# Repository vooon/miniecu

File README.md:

miniECU
=======

miniECU - monitoring unit for model gasoline engines with kill switch.

TBD

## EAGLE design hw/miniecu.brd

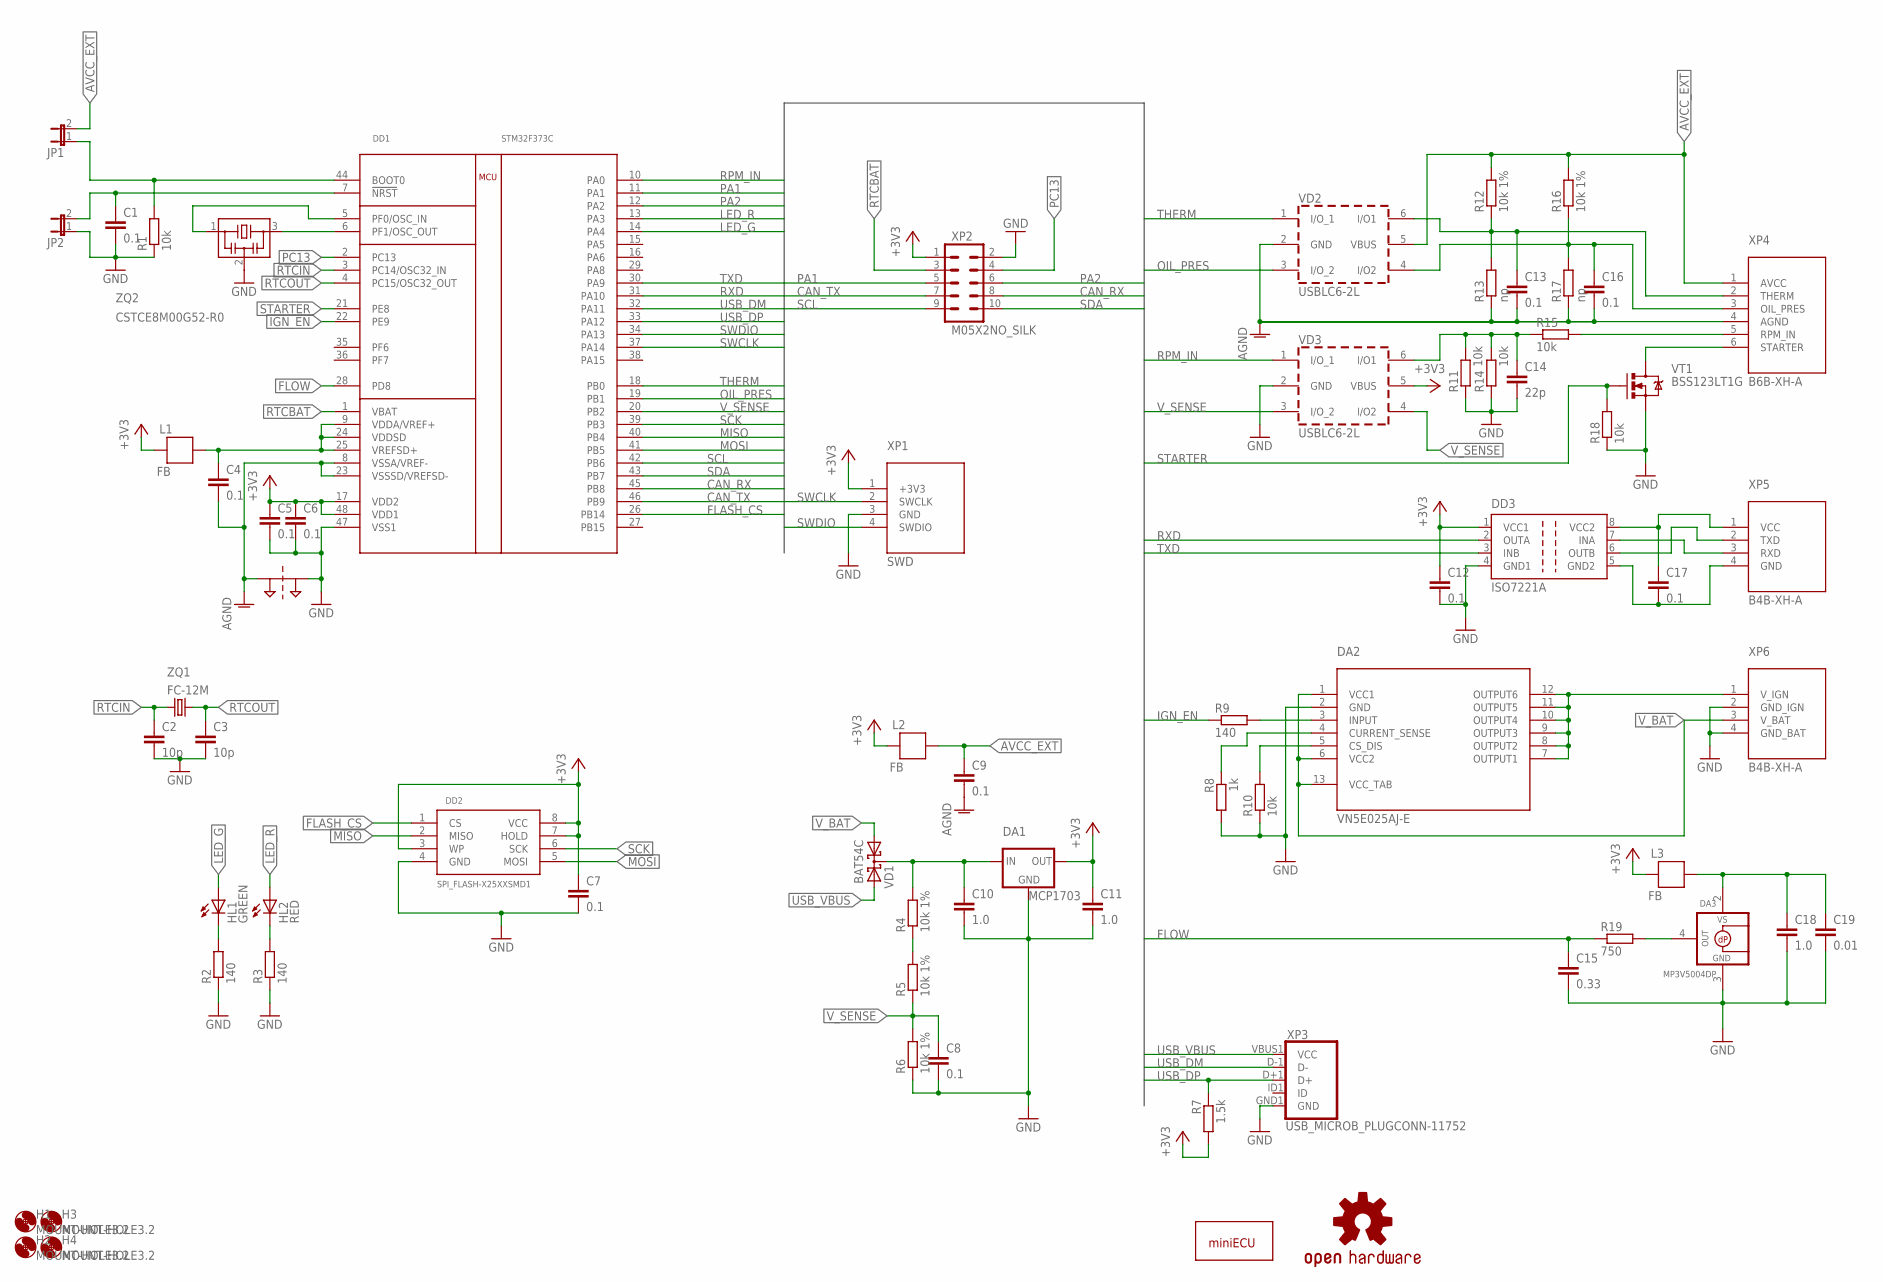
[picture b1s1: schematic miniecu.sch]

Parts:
C1, C4, C5, C6, C7, C8, C9, C12, C13, C16, C17: 0.1; C0603
C2, C3: 10p; C0603
C10, C11, C18: 1.0; C0805
C14: 22p; C0603
C15: 0.33; C0603
C19: 0.01; C0603
DA1: MCP1703; SOT23
DA2: VN5E025AJ-E; POWERSSO-12
DA3: MP3V5004DP; SOP8-1351
DD1: STM32F373C; LQFP48
DD2: SPI_FLASH-X25XXSMD1; SO08-EIAJ
DD3: ISO7221A; SO-08
H1, H2, H3, H4: MOUNT-HOLE3.2; 3,2
HL1: GREEN; LED-0603
HL2: RED; LED-0603
JP1, JP2: JUMPER-2SMD-NO; SJ_2S-NO
L1, L2, L3: FB; 0603
LOGO1: MINIECU_LOGO
LOGO2: OSHW-LOGOL; OSHW-LOGO-L
PT1: 2PT_GND_TIE
R1, R10, R11, R14, R15, R18: 10k; R0603
R2, R3, R9: 140; R0603
R4, R5, R6, R12, R16: 10k 1%; R0805
R7: 1.5k; R0603
R8: 1k; R0603
R13, R17: np; R0805
R19: 750; R0603
VD1: BAT54C; SOT23
VD2, VD3: USBLC6-2L; SOT-23-6L
VT1: BSS123LT1G; SOT23
XP1: SWD; 1X04-1.27MM
XP2: M05X2NO_SILK; 2X5_NOSILK
XP3: USB_MICROB_PLUGCONN-11752; USB-B-MICRO-SMD_V03
XP4: B6B-XH-A; B6B-XH
XP5, XP6: B4B-XH-A; B4B-XH
ZQ1: FC-12M
ZQ2: CSTCE8M00G52-R0; CSTCE

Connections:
!NRST: C1.1, DD1.7 (!NRST), JP2.2
+3V3: C5.1, C6.1, C7.1, C11.1, C12.1, DA1.2 (OUT), DD1.17 (VDD2), DD1.48 (VDD1), DD2.3 (WP), DD2.7 (HOLD), DD2.8 (VCC), DD3.1 (VCC1), L1.2, L2.2, L3.2, R7.2, VD3.5 (VBUS), XP1.1 (+3V3), XP2.1
AGND: C4.2, C9.2, C13.2, C16.2, DD1.8 (VSSA/VREF-), DD1.23 (VSSSD/VREFSD-), PT1.P$1, R13.1, R17.1, VD2.2 (GND), XP4.4 (AGND)
AVCC: C4.1, DD1.9 (VDDA/VREF+), DD1.24 (VDDSD), DD1.25 (VREFSD+), L1.1
AVCC_EXT: C9.1, JP1.2, L2.1, R12.2, R16.2, VD2.5 (VBUS), XP4.1 (AVCC)
AVCC_FLOW: C18.1, C19.1, DA3.2 (VS), L3.1
BOOT0: DD1.44 (BOOT0), JP1.1, R1.2
CAN_RX: DD1.45 (PB8), XP2.8
CAN_TX: DD1.46 (PB9), XP2.7
FLASH_CS: DD1.26 (PB14), DD2.1 (CS)
FLOW: C15.1, DD1.28 (PD8), R19.1
GND: C1.2, C2.2, C3.2, C5.2, C6.2, C7.2, C8.2, C10.2, C11.2, C12.2, C14.2, C15.2, C18.2, C19.2, DA1.1 (GND), DA2.2 (GND), DA3.3 (GND), DD1.47 (VSS1), DD2.4 (GND), DD3.4 (GND1), JP2.1, PT1.P$2, R1.1, R2.1, R3.1, R6.1, R8.2, R10.1, R11.1, R14.1, R18.1, VD3.2 (GND), VT1.2 (S), XP1.3 (GND), XP2.2, XP3.GND1 (GND), XP6.2 (GND_IGN), XP6.4 (GND_BAT), ZQ2.2
GND2: C17.2, DD3.5 (GND2), XP5.4 (GND)
IGN_EN: DD1.22 (PE9), R9.1
IORXD: DD3.7 (INA), XP5.3 (RXD)
IOTXD: DD3.6 (OUTB), XP5.2 (TXD)
LED_G: DD1.14 (PA4), HL1.A
LED_R: DD1.13 (PA3), HL2.A
MISO: DD1.40 (PB4), DD2.2 (MISO)
MOSI: DD1.41 (PB5), DD2.5 (MOSI)
unnamed: R4.1, R5.2
unnamed: DA2.4 (CURRENT_SENSE), R8.1
unnamed: HL2.C, R3.2
unnamed: DA3.4 (+VOUT), R19.2
unnamed: HL1.C, R2.2
unnamed: C10.1, DA1.3 (IN), R4.2, VD1.3 (CC)
unnamed: DA2.3 (INPUT), R9.2
unnamed: DA2.5 (CS_DIS), R10.2
OIL_PRES: C16.1, DD1.19 (PB1), R16.1, R17.2, VD2.3 (I/O_2), VD2.4 (I/O2), XP4.3 (OIL_PRES)
OSC_IN: DD1.5 (PF0/OSC_IN), ZQ2.1
OSC_OUT: DD1.6 (PF1/OSC_OUT), ZQ2.3
PA1: DD1.11 (PA1), XP2.5
PA2: DD1.12 (PA2), XP2.6
PC13: DD1.2 (PC13), XP2.4
RPM_IN: C14.1, DD1.10 (PA0), R11.2, R14.2, R15.1, VD3.1 (I/O_1), VD3.6 (I/O1)
RPM_IN_CON: R15.2, XP4.5 (RPM_IN)
RTCBAT: DD1.1 (VBAT), XP2.3
RTCIN: C2.1, DD1.3 (PC14/OSC32_IN), ZQ1.1
RTCOUT: C3.1, DD1.4 (PC15/OSC32_OUT), ZQ1.2
RXD: DD1.31 (PA10), DD3.2 (OUTA)
SCK: DD1.39 (PB3), DD2.6 (SCK)
SCL: DD1.42 (PB6), XP2.9
SDA: DD1.43 (PB7), XP2.10
STARTER: DD1.21 (PE8), R18.2, VT1.1 (G)
STARTER_OUT: VT1.3 (D), XP4.6 (STARTER)
SWCLK: DD1.37 (PA14), XP1.2 (SWCLK)
SWDIO: DD1.34 (PA13), XP1.4 (SWDIO)
THERM: C13.1, DD1.18 (PB0), R12.1, R13.2, VD2.1 (I/O_1), VD2.6 (I/O1), XP4.2 (THERM)
TXD: DD1.30 (PA9), DD3.3 (INB)
USB_DM: DD1.32 (PA11), XP3.D-1 (D-)
USB_DP: DD1.33 (PA12), R7.1, XP3.D+1 (D+)
USB_VBUS: VD1.2 (A2), XP3.VBUS1 (VCC)
VCC2: C17.1, DD3.8 (VCC2), XP5.1 (VCC)
V_BAT: DA2.1 (VCC1), DA2.6 (VCC2), DA2.13 (VCC_TAB), VD1.1 (A1), XP6.3 (V_BAT)
V_IGN: DA2.7 (OUTPUT1), DA2.8 (OUTPUT2), DA2.9 (OUTPUT3), DA2.10 (OUTPUT4), DA2.11 (OUTPUT5), DA2.12 (OUTPUT6), XP6.1 (V_IGN)
V_SENSE: C8.1, DD1.20 (PB2), R5.1, R6.2, VD3.3 (I/O_2), VD3.4 (I/O2)

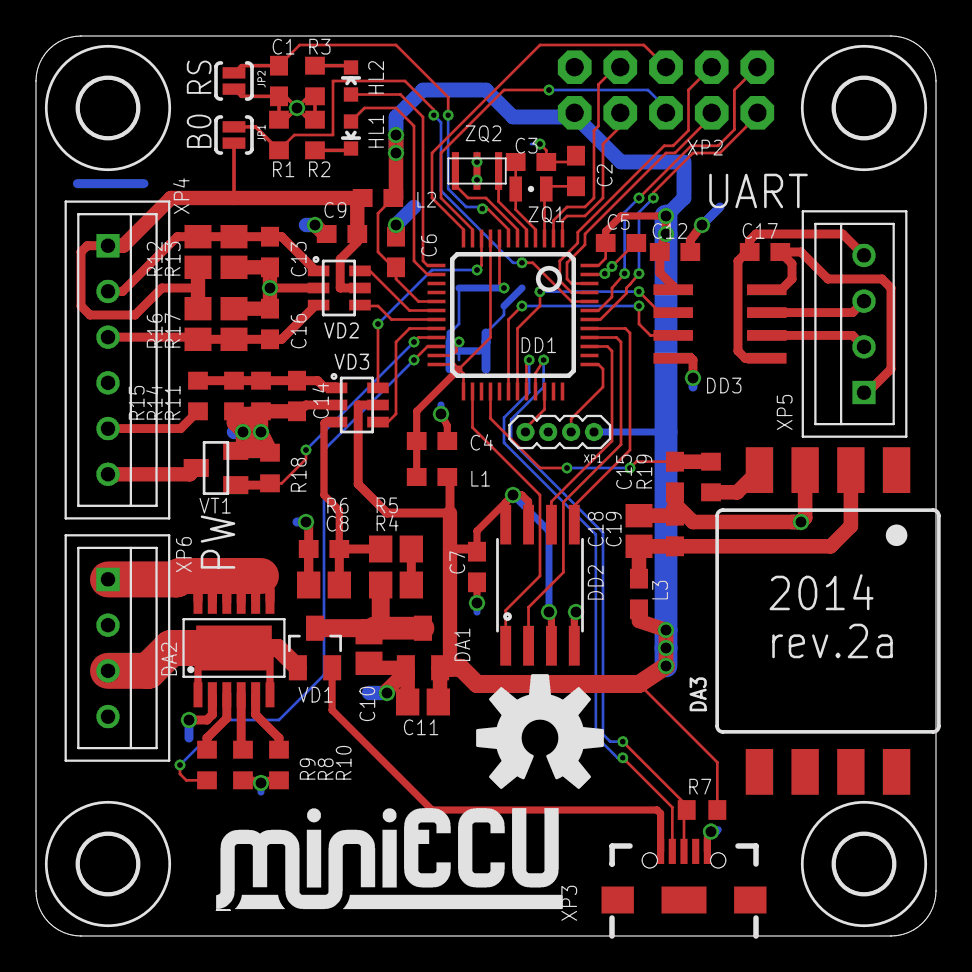
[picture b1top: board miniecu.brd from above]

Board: 2 copper layers, 50.0 x 50.0 mm, 70 parts (1 on the bottom side), 56 nets.

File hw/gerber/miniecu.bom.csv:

"Qty";"Value";"Device";"Package";"Parts";"Description";"FREQUENCY";"MF";"MPN";"OC_FARNELL";"OC_MOUSER";"OC_NEWARK";"PROD_ID";"VALUE";
"2";"";"JUMPER-2SMD-NO";"SJ_2S-NO";"JP1, JP2";"Jumper";"";"";"";"";"";"";"";"";
"1";"0.01";"C-EUC0603";"C0603";"C19";"CAPACITOR, European symbol";"";"";"";"";"";"";"";"";
"11";"0.1";"C-EUC0603";"C0603";"C1, C4, C5, C6, C7, C8, C9, C12, C13, C16, C17";"CAPACITOR, European symbol";"";"";"";"";"";"";"";"";
"1";"0.33";"C-EUC0603";"C0603";"C15";"CAPACITOR, European symbol";"";"";"";"";"";"";"";"";
"3";"1.0";"C-EUC0805";"C0805";"C10, C11, C18";"CAPACITOR, European symbol";"";"";"";"";"";"";"";"";
"1";"1.5k";"R-EU_R0603";"R0603";"R7";"RESISTOR, European symbol";"";"";"";"";"";"";"";"";
"6";"10k";"R-EU_R0603";"R0603";"R1, R10, R11, R14, R15, R18";"RESISTOR, European symbol";"";"";"";"";"";"";"";"";
"5";"10k 1%";"R-EU_R0805";"R0805";"R4, R5, R6, R12, R16";"RESISTOR, European symbol";"";"";"";"";"";"";"";"";
"3";"140";"R-EU_R0603";"R0603";"R2, R3, R9";"RESISTOR, European symbol";"";"";"";"";"";"";"";"";
"1";"1k";"R-EU_R0603";"R0603";"R8";"RESISTOR, European symbol";"";"";"";"";"";"";"";"";
"1";"22p";"C-EUC0603";"C0603";"C14";"CAPACITOR, European symbol";"";"";"";"";"";"";"";"";
"1";"2PT_GND_TIE";"2PT_GND_TIE";"2PT_GND_TIE";"PT1";"Package for connecting two ground nets in one place.";"";"";"";"";"";"";"";"";
"2";"6p";"C-EUC0603";"C0603";"C2, C3";"CAPACITOR, European symbol";"";"";"";"";"";"";"";"";
"1";"750";"R-EU_R0603";"R0603";"R19";"RESISTOR, European symbol";"";"";"";"";"";"";"";"";
"1";"B4B-XH-A";"IGN_POWER-B4B-XH-A";"B4B-XH";"XP6";"JST XH CONNECTOR";"";"";"";"";"";"";"";"";
"1";"B4B-XH-A";"UART-B4B-XH-A";"B4B-XH";"XP5";"JST XH CONNECTOR";"";"";"";"";"";"";"";"";
"1";"B6B-XH-A";"SENSORS-B6B-XH-A";"B6B-XH";"XP4";"JST XH CONNECTOR";"";"";"";"";"";"";"";"";
"1";"BAT54C";"BAT54C";"SOT23";"VD1";"Schottky Diodes";"";"";"";"";"";"";"";"";
"1";"BSS123LT1G";"MOSFET-NCHANNELBSS123LT1G";"SOT23";"VT1";"Common NMOSFET Parts";"";"";"";"";"";"";"TRANS-08345";"";
"1";"CSTCE8M00G52-R0";"CSTCE8M00G52-R0";"CSTCE";"ZQ2";"Resonator";"8 MHz";"";"";"";"81-CSTCE8M00G52-R0";"";"";"";
"3";"FB";"FB";"0603";"L1, L2, L3";"";"";"";"";"";"";"";"";"";
"1";"FC-12M";"FC-12M";"FC-12M";"ZQ1";"kHz RANGE CRYSTAL UNIT";"";"";"";"";"";"";"";"";
"1";"GREEN";"LED-GREEN0603";"LED-0603";"HL1";"Various green LEDs";"";"";"";"";"";"";"DIO-00821";"GREEN";
"1";"ISO7221A";"ISO7221A";"SO-08";"DD3";"DUAL DIGITAL ISOLATORS";"";"";"ISO7221AD";"1390651";"";"48M0672";"";"";
"1";"M05X2NO_SILK";"M05X2NO_SILK";"2X5_NOSILK";"XP2";"Header 5x2";"";"";"";"";"";"";"";"";
"1";"MCP1703";"MCP1700SOT-23";"SOT23";"DA1";"VOLTAGE REGULATOR";"";"";"";"";"";"";"";"";
"1";"MINIECU_LOGO";"MINIECU_LOGO";"MINIECU_LOGO";"LOGO1";"Logo imported from bmp.";"";"";"";"";"";"";"";"";
"4";"MOUNT-HOLE3.2";"MOUNT-HOLE3.2";"3,2";"H1, H2, H3, H4";"MOUNTING HOLE with drill center marker";"";"";"";"";"";"";"";"";
"1";"MP3V5004DP";"MPXV7025DP";"SOP8-1351";"DA3";"PRESSURE SENSOR - Differential Input, Single-Ended Output";"";"";"";"";"";"";"";"";
"1";"OSHW-LOGOL";"OSHW-LOGOL";"OSHW-LOGO-L";"LOGO2";"Open Source Hardware Logo This logo indicates the piece of hardware it is found on incorporates a OSHW license and/or adheres to the definition of open source hardware found here: http://freedomdefined.org/OSHW";"";"";"";"";"";"";"";"";
"1";"RED";"LED-RED0603";"LED-0603";"HL2";"Assorted Red LEDs";"";"";"";"";"";"";"DIO-00819";"RED";
"1";"SPI_FLASH-X25XXSMD1";"SPI_FLASH-X25XXSMD1";"SO08-EIAJ";"DD2";"8pin SPI Flash series x25xx. Works with devices like W25X32 and BR25L32";"";"";"";"";"";"";"";"";
"1";"STM32F373C";"STM32F373C";"LQFP48";"DD1";"STM32F373";"";"";"";"";"";"";"";"";
"1";"SWD";"SWD";"1X04-1.27MM";"XP1";"";"";"";"";"";"";"";"";"";
"2";"USBLC6-2L";"USBLC6-2SC6";"SOT-23-6L";"VD2, VD3";"VERY LOW CAPACITANCE ESD PROTECTION 2 line";"";"";"";"";"";"";"";"";
"1";"USB_MICROB_PLUGCONN-11752";"USB_MICROB_PLUGCONN-11752";"USB-B-MICRO-SMD_V03";"XP3";"USB Micro-B Plug";"";"";"";"";"";"";"CONN-11752";"";
"1";"VN5E025AJ-E";"VN5E025AJ-E";"POWERSSO-12";"DA2";"Single channel high-side driver with analog current sense";"";"";"";"";"";"";"";"";
"2";"np";"R-EU_R0805";"R0805";"R13, R17";"RESISTOR, European symbol";"";"";"";"";"";"";"";"";

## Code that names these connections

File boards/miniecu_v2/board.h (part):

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/*
 * GPIOA setup:
 *
 * PA0  - RPM IN                    (alternate 1).
 * PA1  - XP2 PA1                   (def).
 * PA2  - XP2 PA2                   (def).
 * PA3  - LED RED                   (output).
 * PA4  - LED GREEN                 (output).
 * PA5  -                           (def).
 * PA6  -                           (def).
 * PA7  -                           (def).
 * PA8  -                           (def).
 * PA9  - TXD                       (alternate 7).
 * PA10 - RXD                       (alterante 7).
 * PA11 - USB D+                    (alternate 14).
 * PA12 - USB D-                    (alternate 14).
 * PA13 - SWDIO                     (alternate 0).
 * PA14 - SWCLK                     (alternate 0).
 * PA15 -                           (def).
 */
#define VAL_GPIOA_MODER             (PIN_MODE_ALTERNATE(GPIOA_RPM_IN) |     \
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/*
 * GPIOB setup:
 *
 * PB0  - THERM                     (analog floating).
 * PB1  - OIL Pessure               (analog floating).
 * PB2  - V Sense                   (analog floating).
 * PB3  - SPI1 SCK                  (alternate 5).
 * PB4  - SPI1 MISO                 (alternate 5).
 * PB5  - SPI1 MOSI                 (alternate 5).
 * PB6  - I2C1 SCL                  (alternate 4).
 * PB7  - I2C1 SDA                  (alternate 4).
 * PB8  - CAN RX                    (alternate 9).
 * PB9  - CAN TX                    (alternate 9).
 * PB10 -                           (def).
 * PB11 -                           (def).
 * PB12 -                           (def).
 * PB13 -                           (def).
 * PB14 - FLASH_CS                  (output up).
 * PB15 -                           (def).
 */
#define VAL_GPIOB_MODER             (PIN_MODE_ANALOG(GPIOB_THERM) |         \
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 * PC10 -                           (def).
 * PC11 -                           (def).
 * PC12 -                           (def).
 * PC13 - XP2 PC13                  (def).
 * PC14 - OSC32_IN                  (input floating).
 * PC15 - OSC32_OUT                 (input floating).
 */
#define VAL_GPIOC_MODER             (PIN_MODE_INPUT(GPIOC_PIN0) |           \
                                     PIN_MODE_INPUT(GPIOC_PIN1) |           \
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 * PD5  -                           (def).
 * PD6  -                           (def).
 * PD7  -                           (def).
 * PD8  - FLOW analog in            (analog floating).
 * PD9  -                           (def).
 * PD10 -                           (def).
 * PD11 -                           (def).
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 * PE5  -                           (def).
 * PE6  -                           (def).
 * PE7  -                           (def).
 * PE8  - STARTER                   (output).
 * PE9  - IGN_EN                    (output).
 * PE10 -                           (def).
 * PE11 -                           (def).
 * PE12 -                           (def).
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/*
 * GPIOF setup:
 *
 * PF0  - OSC IN                    (input floating).
 * PF1  - OSC OUT                   (input floating).
 * PF2  -                           (def).
 * PF3  -                           (def).
 * PF4  -                           (def).
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
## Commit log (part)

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2014-01-20 initial:
2014-01-20 add connectors (made from bt_con-jst-xh.lbr)
2014-01-20 fix pad names
2014-01-20 add isolator, esd lib
2014-01-20 add VN5E025 smart switch
2014-01-21 change iv esd supply +3V3->AVCC
2014-01-21 initial pcb: placing done
2014-01-21 use two resistors in voltage divider
2014-01-22 pcb: routing done
2014-01-22 brd: place components >Name
2014-01-22 pcb: add bottom silk
2014-01-22 pcb: gerbers for IDTEAD Studio
2014-01-22 eagle: move project description
    Setup your environment:
    - ~/src/miniecu (git repo)
    - ~/eagle/miniecu soft link to ~/src/miniecu/hw
2014-01-23 sch: change LDO MCP1700 (6V max) -> MCP1703 (16V max) in the same package
    Fix LDO ceramic capasitance from 4.7 µF to 1.0 µF (MCP1703 DS)
2014-01-23 hw: release hw v1b, update gerbers
2014-01-30 hw: release v1c & update gerbers
    changes from v1b:
    - Use rounded corners.
    - Add one GND drill.
2014-02-02 move datasheets to doc/datasheets
2014-02-02 Add nanopb - library for message encoding/decoding
2014-02-02 pb: Add initial protocol defenition
2014-02-02 fw: Add board defenition, stub project
    New dirs:
    - boards -- chibios board definition + project defenition (makefile)
    - fw -- firmware sources
2014-02-02 pb: Add PARAM & LOG definitions
2014-02-03 fw: Add nanopb to build
2014-02-03 fw: Add simulator platform
2014-02-04 pb: fix spelling error
2014-02-05 tool: Implement PBstx protocol
2014-02-05 fw: Implement PBstx protocol framing
    Simple protocol for transfering Protocol Buffers messages.
2014-02-07 pb: Add engine_id to all messages
    Fix nanopb options.
2014-02-07 fw: Add communication task
    All communications with gcs/fcu in th_comm.
2014-02-07 fw: add message decoding for TimeReference
2014-02-07 fw: Minimize memory usage by RTOS & nanopb
2014-02-08 fw: fix pbstx rx
2014-02-08 update nanopb
2014-02-09 fw: port to ChibiOS/Nil 3.0 (dev version)
    TODO: Simulator broken.
    Current kernel_3_dev supports only ARM arch.
    Need to port SIMIA32 to new ChibiOS version.
2014-02-14 update ext nanopb & ChibiOS
2014-02-14 remove simulator target
    Currently ChibiOS 3.0 don't support simulator target.
    Instead of porting simulator i've decided use vl-discovery for testing.
2014-02-15 fw: move build to subdir
2014-02-15 fw: switch to ChibiOS/Nil only.
    And some debug stuff for VL-Discovery.
2014-02-25 update ext libs.
2014-02-25 fw: sync Nil configuration.
2014-02-25 fw: commit debug code before reverting to ChibiOS/RT 2.x
    Some very strange bugs with serial io in ChibiOS/Nil 3.
    And we dicide move to STM32 F3 (it's only x2 price of F0 in TSOP-48, but much more
    horse power).
2014-02-26 fw: add led indication on hw_v1c.
    NOTE: almost all flash used :(
2014-02-26 fw: use main as idle thread
2014-02-27 hw: save hw_1.0c board
2014-02-27 hw: add stm32f373 library
2014-03-01 hw: replace mcu
2014-03-06 add datasheet for SST25
2014-03-06 update chibios
2014-03-06 fw: temp. switch to flash25 test app
2014-03-07 fw: update flash driver
2014-03-09 hw: do half connections of v2
2014-03-09 hw: add SWD, EXT connectors; sch done
2014-03-09 hw: split miniecu.lbr to logo and con libs
2014-03-09 hw: route top half
2014-03-09 hw: release hw_2.0a
2014-03-12 hw: Update description, add BOM in CSV
2014-04-15 Update flash lib
2014-04-15 Update nanopb lib
2014-04-15 fw: Remove VL Discovery target
2014-04-15 fw: Disable miniecu_v1 target
    V1 will be dropped later (because 16 KiB of FLASH not enougth for ChibiOS based
    firmware).
2014-04-17 fw: Add ADC thread
    Currently it does nothing.
2014-04-17 fw: refactoring protocol, add StatusText message
2014-04-17 fw: drop ChibiOS/Nil support, fix LED initialization
2014-04-18 fw: test internal termometer
    ADC1: works, 50 kHz
    SDADC1 & SDADC3: strange result, but isr fires at 2 kHz & 25 kHz
2014-04-20 fw: SDADC test passed, TODO fix sma_*()
2014-04-21 fw: ADC: remove SMA and setup events for update.
    TODO: add conversion logick to adc thread (some conversion done by
    cb's).
2014-04-21 fw: Param subsystem
2014-04-22 fw: update chibios
2014-04-23 fw: Add RTC module, enable TimeReference
2014-04-23 fw: Add Vbat to Status
    TODO: battery remaining calculation based on BATT_TYPE & BATT_CELLS
    and voltage.
2014-04-23 fw: Fix battery cutoff values
2014-04-24 fw: fix float param set, implement SN param.
    SN filled by rules for F4 DFU (similar to F3 except 2 low bytes).
2014-04-24 fw: Enable NTC term input, temperature field in Status
2014-05-08 Switch ChibiOS to stable branch (2.6.x)
2014-05-08 fw: Move internal (flash) messages to flash.proto
    Miniecu.proto for protocol messages only.
    Flash.proto for internal flash messages.
2014-05-08 fw: Implement USB serial for configuration & log download
    NOTE: USB not isolated from ignition battery! Do not enable ign power!
2014-05-25 fw: Add memory dump command
    Issues #5, #6.
2014-05-25 fw: Send ADC RAW voltages if required
    Fix #6.
2014-05-25 fw: Fix USB reconnect
    Fix #7.
2014-05-26 fw: RPM module
    Fix #2.
2014-05-30 tools: Fix PBStx __die__() exception
    New: memdump tool (WIP)
2014-05-30 fw: Initial flash_log module.
    New: Memdump flash.
    Fix #5.
2014-05-30 fw: Command module (initial)
    Currently supports only Ignition and Starter operations.
    Fix: #10.
2014-05-30 fw: Initial param save function
    Partial #4.
2014-05-30 fw: Parameters now save on flash
    TODO: load.
    Part of #4.
2014-05-31 fw: Add parameter stream terminator
    Remove debugging messages.
    Part of #4.
2014-05-31 fw: Response to config save/load/erase
    TODO: wait end of operation (condvar broken)
    Part of #4.
2014-06-01 fw: Save/Load/Erase parameters done.
    Fix #4.
2014-06-02 fw: Add ESTOP in command module
    Small changes: don't answer to broadcast commands,
    add python protoc generator.
    Fix #10.
2014-06-02 Ext update
2014-06-02 fw: Serial baudrate change
    Fix #14.
2014-06-02 fw: OILP ADC submodule.
    Currently only two modes: Disabled, NTC10k (secondary engine termometer).
    Fix #11. And fix negative engine temperature.
2014-06-03 tools: pep8
2014-06-04 fw: FLOW submodule
    TODO: calculate total_used_ml.
    Fix #3.
2014-09-23 hw: Release hw_2.0a.
2014-09-23 fw: Remove board file for hw_1.0, it never works.
2014-09-23 Update ChibiOS 2.6.
2014-09-23 Update ChibiOS repo path.
2014-09-23 fw: Build failed at flash25 module.
2014-09-23 Upgrade flash25 for ChibiOS v3.
2014-09-23 Upgrade for ChibiOS v3. Builds.
    RTC support broken (no HAL driver).
2014-09-24 fw: Refactoring PBStx module to frame-only proto.
    New proto: STX, SEQ, LEN_LSB, LEN_MSB, PAYLOAD..., CRC16_LSB, CRC16_MSB
2014-09-24 fw: Update pktview.py to new proto model
2014-09-24 fw: th_comm now sends status.
2014-09-26 Update submodules.
2014-09-26 fw: #20. Update proto: simplify command, mesurement units.
2014-09-26 fw #20: fix compile
2014-09-26 fw #20: Enable debug_printf()
2014-09-26 fw #19: update alert_led module
2014-09-26 fw #20: Remove FSM from pbstxReceive. Dynamic USB instance.
2014-09-26 fw #21: create parameter definition file
2014-09-26 fw #21: explicit string def not needed
2014-09-26 tool #21: var tag
2014-09-27 fw #21: add param table template
2014-09-27 fw #21: pgen tool almost done
2014-09-27 fw #21: Add read only/don't save flags to generator.
2014-09-27 fw #21: fix c-lang errors
2014-09-27 fw #21: almost work, need reorganize flash module
2014-09-29 tools #21: make constants extern
2014-09-29 fw #21: param_save()/load() in param module
2014-09-30 fw #19: Update RTC module. Also now it check state at init.
2014-09-30 fw: Update ChibiOS (RTC dayofweek fix)
2014-09-30 hw: Update eagle project file.
2014-09-30 fw #19: Update command module, not finished.
    Update memdump, but it still don't work.
2014-09-30 fw #16: remove memdump. Trying to find error source
2014-09-30 fw: Fix memdump bug
2014-09-30 tools: Improve memdump tool.
2014-09-30 fw: param load at startup almost done.
    Buggy stopper: param_load() freeze cpu if it called from main().
    So as workaroud i decide to load params in flash log thread.
2014-09-30 fw: Move th_flash_log to subdir log. Add lib.mk.
    Now thread priorities and stack size defined in fw_config.h
2014-10-01 tool: add sql_log module (require sqlalchemy)
2014-10-01 tools: Add logging to pktview tool.
2014-10-01 tool: Add logging to memdump
2014-10-01 tool: reduce copy-paste at logging wrapper.
2014-10-02 tools #17: Decided to write CCGui using PyQt/PySide.
2014-10-02 tools #17: On Ubuntu python2 Qt bindings for Qt5 not available.
    Decided to give a try to Gtk 3.
2014-10-02 tool #17: parameter model.
2014-10-02 fw: Add ParamRequset ony by index.
2014-10-02 tools #17: param retrive/sync operations.
2014-10-02 tools #17: add status and status_text managers. Enable logging.
2014-10-03 tools #17: add glade fule for connection dialog
2014-10-03 #17: Move UI classes to ui.
2014-10-03 #17: global glade builder
2014-10-03 #17: fill combobox items
2014-10-03 #17: create a connection using dialog data
2014-10-03 #17: add param tab button handlers
2014-10-09 ccgui #17: Rename *.glade files to GtkBuilder *.ui.
2014-10-09 ccgui #17: add param listbox widget
2014-10-09 ccgui #17: Add sig-slot to param model.
2014-10-09 ccgui #17: add signal to status model.
2014-10-09 ccgui #17: Add CommandManager. Now settings tab fully functional.
2014-10-09 ccgui #17: Load param definitions from file. Parameters tab complete.
2014-10-14 ccgui: start porting gtkgauge.{c,h} to python
2014-10-14 ccgui: draw GYR strips
2014-10-14 ccgui: draw YOR,ROY,RYG strips
2014-10-14 ccgui: fix strip draw eqations
2014-10-14 ccgui: draw numbers
2014-10-14 ccgui: draw screws
2014-10-14 ccgui: draw gauge name
2014-10-15 ccgui: draw guage hand
2014-10-15 ccgui: Complete porting GtkGauge widget.
    TODO: move hand with some acceleration, not instantly.
2014-10-16 ccgui: Split GtkGauge.draw_static_base to several functions.
2014-10-16 ccgui: Remove unneded log prints from GtkGauge.
2014-10-16 ccgui: GtkGauge add smooth_interval.
2014-10-16 ccgui #18: Status tab.
2014-10-16 ccgui #18: Add time sync.
    Also automatic param pull on start.
2014-10-16 pb: Revert TemperatureStatus to engine1,2.
2014-10-16 ccgui #18: enable logging
2014-10-16 fw: Add comm.mk
2014-10-16 fw: Add log.mk.
2014-10-16 make: Automatically update python pb2 files
2014-10-16 pgen: Add defines for parameter values.
2014-10-16 fw: Reenable RPM module. Now it use polled ICU API.
    Not tested.
2014-10-17 ccgui: Update temperature filed.
2014-10-17 fw: Rewrite PRM back to callback. Fonund bug in icuGetPeriodX().
    Issue #23.
2014-10-18 fw: Enable ChibiOS debugging.
    Issue #23.
2014-10-18 fw #19: chThdWait() already has chThdRelease().
    Additional release cause halt,
    but because assertions been turned off, I did not see it.
2014-10-18 ccgui #18: Enable io logging: now it not works because #22.
2014-10-18 fw #19: Remove not working filter from th_rpm.
    Need to find usable filter algo for this data.
2014-10-18 fw #19: RPM module now works again.
    Returned to average with circular buffer,
    cummulative don't work for unknown reason.
2014-10-18 fw #19: Add SERIAL1 proto selector.
2014-10-18 fw #19: Reenable ADC thread. Now works only ADC1 (cpu temp, vrtc).
2014-10-18 fw #19: Disable adc filters
2014-10-18 fw #19: Enable SDADC3: bug in driver.
    Wrong rccEnable in adc_lld.c at line 447 (waiting upstream fix).
2014-10-18 fw: Switch ChibiOS mirror, i hope it updates soon
2014-10-22 ext: Use ChibiOS from SVN because git mirror now not updates.
2014-10-22 chibios: remove folder.
2014-10-22 fw: Remove compiler warnings.
2014-10-22 ccgui: Fix #22: sqlite threading error.
2014-10-22 ccgui #18: Do param sync before save
2014-10-22 fw: changes for FLOW testing
2014-10-28 ccgui #18: Add switches to control IGNITION and STARTER power.
2014-10-28 fw: Rename battery voltage trimmer parameter.
2014-10-28 fw: Send unfilered data, enable filters.
2014-10-28 tools: Add logutil
2014-10-28 tools: Add log CSV export.

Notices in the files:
boards/miniecu_v2/board.h:
ChibiOS/RT - Copyright (C) 2006-2014 Giovanni Di Sirio
Licensed under the Apache License, Version 2.0 (the "License");
parts and their libraries:
SparkFun-DigitalIC: Licensing: CC v3.0 Share-Alike You are welcome to use this library for commercial purposes.
microbuilder: This work is placed in the public domain, and may be freely used for commercial and non-commercial work with the following conditions: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
